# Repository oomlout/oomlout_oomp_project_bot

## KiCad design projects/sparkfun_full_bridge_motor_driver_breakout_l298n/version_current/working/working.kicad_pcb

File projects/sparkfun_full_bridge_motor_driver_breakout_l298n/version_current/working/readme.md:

# Full_Bridge_Motor_Driver_Breakout-L298N by sparkfun  
This is a harvested standardized copy of a project from github.  
The original project can be found at:  
https://github.com/sparkfun/Full_Bridge_Motor_Driver_Breakout-L298N  
Please consult that link for additional, details, files, and license information.  
Note: It was auto harvested and if the original repo had more than one board file or anything out of the ordinary the files here are likely not representative.

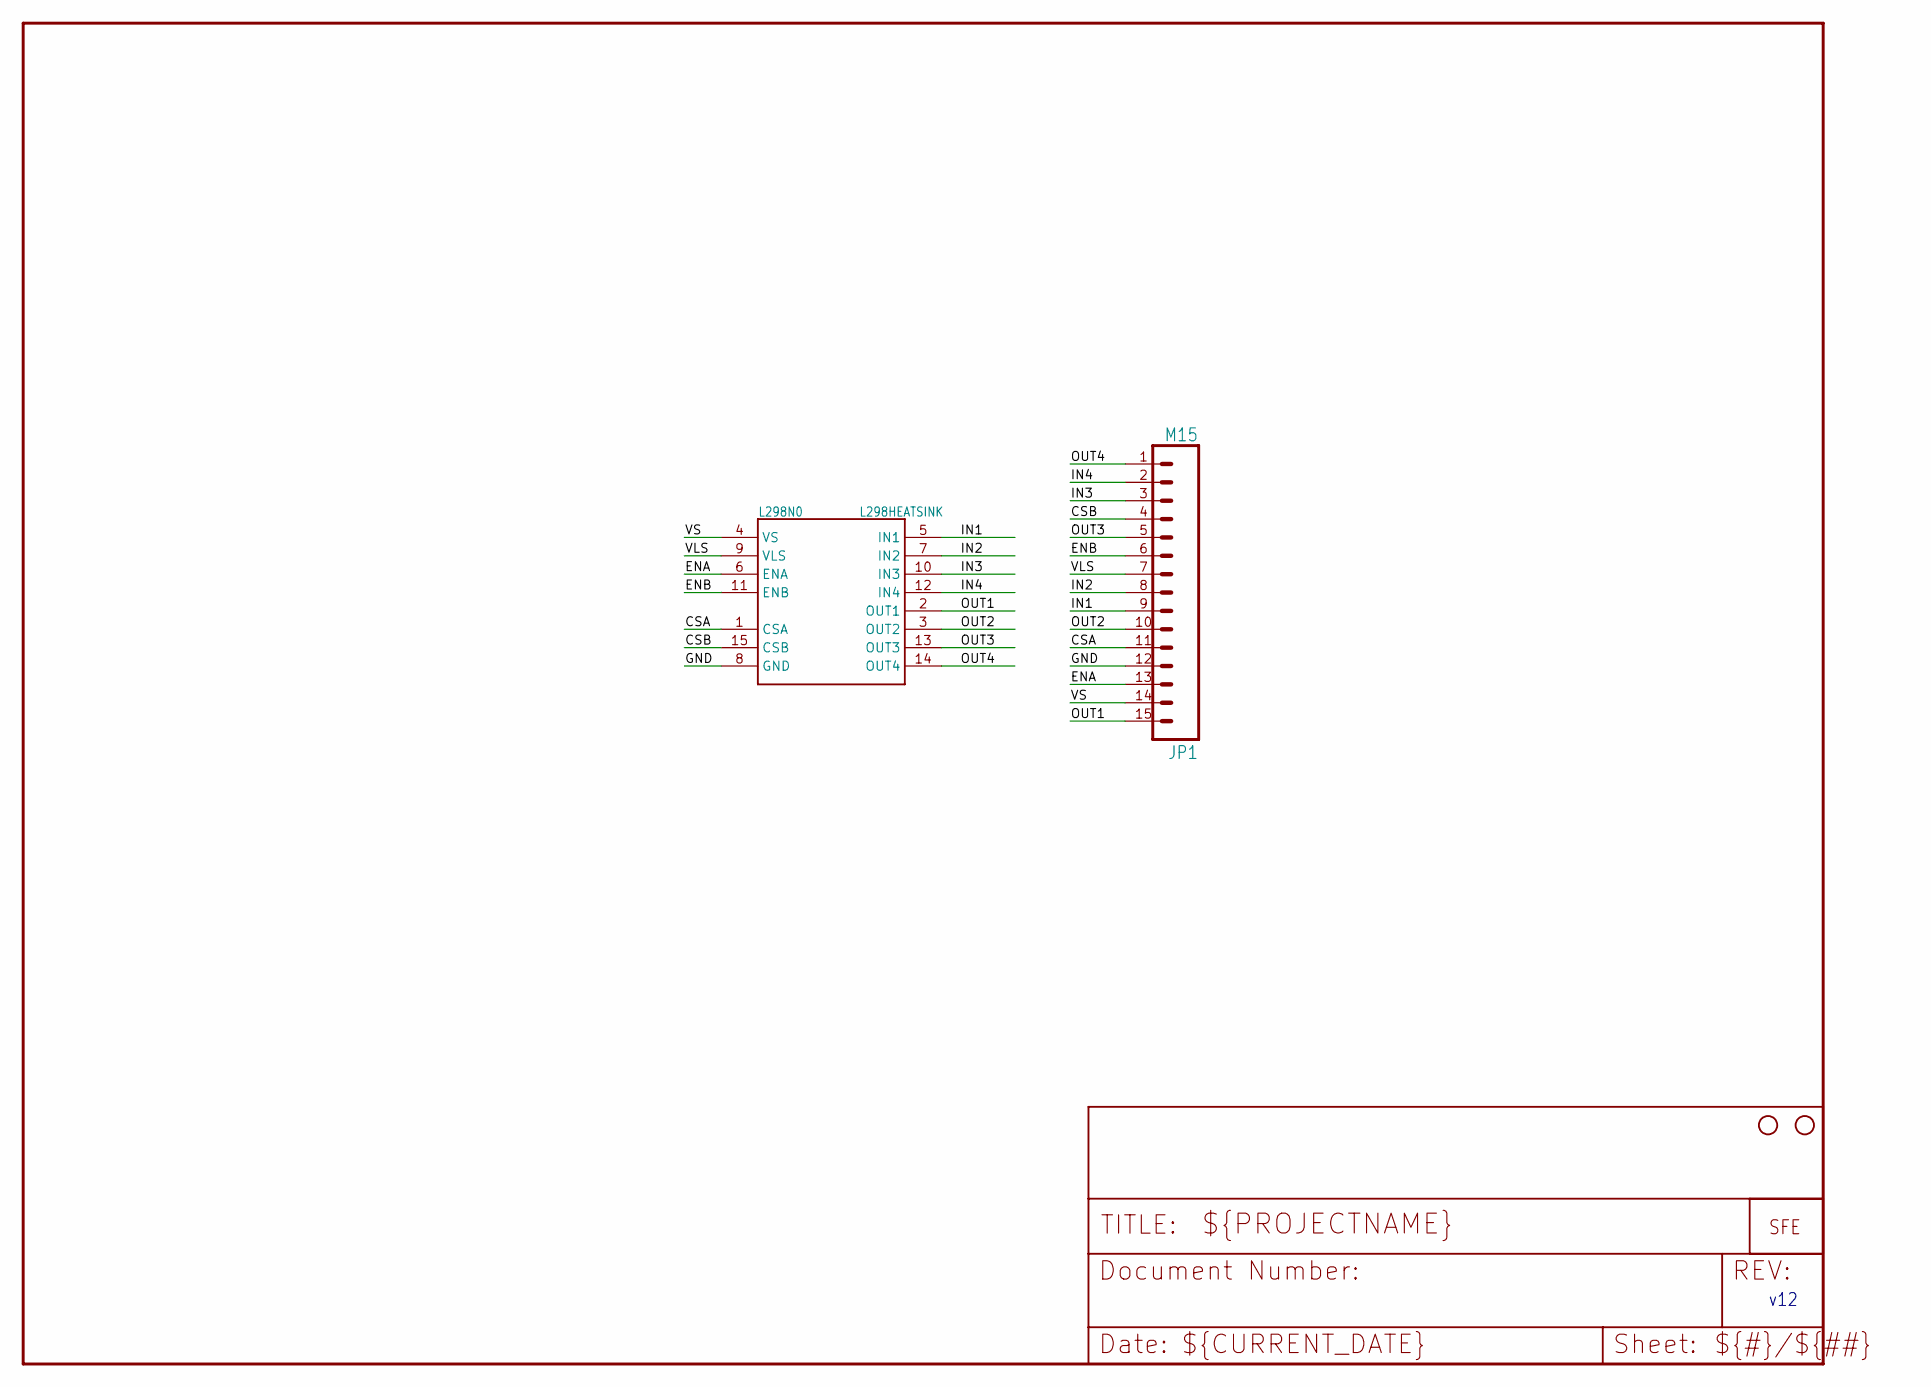
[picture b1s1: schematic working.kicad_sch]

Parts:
JP1: M15; 1X15
JP2, JP3: STAND-OFF
JP4: LOGO-SFENEW; SFE-NEW-WEBLOGO
L298N0: L298HEATSINK; MULTIWATT15_6400BGHEATSINK

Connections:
CSA: JP1.11, L298N0.1 (CSA)
CSB: JP1.4, L298N0.15 (CSB)
ENA: JP1.13, L298N0.6 (ENA)
ENB: JP1.6, L298N0.11 (ENB)
GND: JP1.12, L298N0.8 (GND)
IN1: JP1.9, L298N0.5 (IN1)
IN2: JP1.8, L298N0.7 (IN2)
IN3: JP1.3, L298N0.10 (IN3)
IN4: JP1.2, L298N0.12 (IN4)
OUT1: JP1.15, L298N0.2 (OUT1)
OUT2: JP1.10, L298N0.3 (OUT2)
OUT3: JP1.5, L298N0.13 (OUT3)
OUT4: JP1.1, L298N0.14 (OUT4)
VLS: JP1.7, L298N0.9 (VLS)
VS: JP1.14, L298N0.4 (VS)

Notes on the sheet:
v12

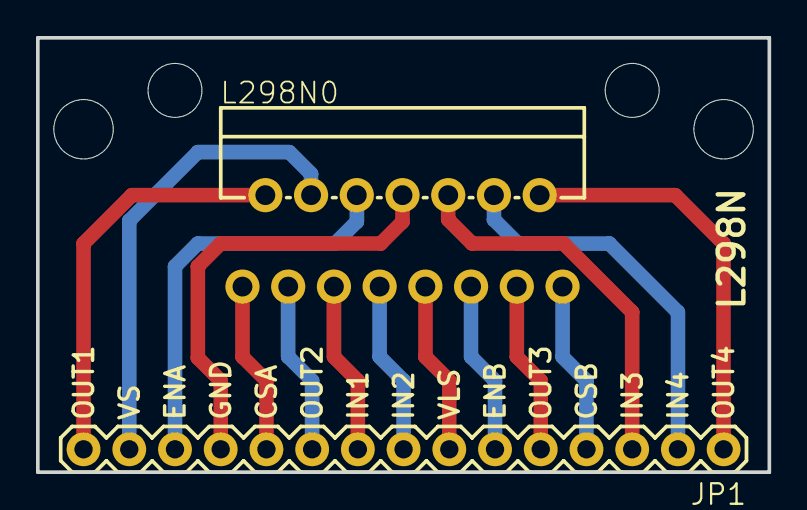
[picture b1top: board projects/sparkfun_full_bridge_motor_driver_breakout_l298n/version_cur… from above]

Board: 2 copper layers, 40.6 x 24.1 mm, 5 parts (1 on the bottom side), 15 nets.

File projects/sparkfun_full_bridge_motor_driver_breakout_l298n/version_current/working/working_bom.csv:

Row,Description,Part,References,Value,Footprint,Quantity Per PCB,Status,Datasheet
1,,LOGO-SFENEW,JP4,LOGO-SFENEW,SFE-NEW-WEBLOGO,1, ,
2,,M15,JP1,M15,1X15,1, ,
3,,STAND-OFF,JP2 JP3,STAND-OFF,STAND-OFF,2, ,
4,,L298HEATSINK,L298N0,L298HEATSINK,MULTIWATT15_6400BGHEATSINK,1, ,





Project info:
Schematic:,working
Variant:,default
Revision:,
Date:,2023-08-06_12-56-02
KiCad Version:,7.0.6-7.0.6~ubuntu22.04.1
Statistics:
Component Groups:,4
Component Count:,5 (0 SMD/ 0 THT)
Fitted Components:,5 (0 SMD/ 0 THT)
Number of PCBs:,1
Total Components:,5

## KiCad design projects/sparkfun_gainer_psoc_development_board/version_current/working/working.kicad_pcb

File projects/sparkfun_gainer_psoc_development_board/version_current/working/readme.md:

# OOMP Project  
## Gainer_PSoC_Development_Board  by sparkfun  
  
oomp key: oomp_projects_flat_sparkfun_gainer_psoc_development_board  
(snippet of original readme)  
  
SparkFun Gainer PSoC Development Board  
========================================  

[*SparkFun Gainer PSoC Development Board (DEV-08480)*](https://www.sparkfun.com/products/8480)  
  
This board utilizes the Cypress PSoC CY8C29466 IC making it a great board for digital and analog projects where AtoD and DtoA is required.  
 Simple USB interface for reprogramming - no external programmer needed.  
  
Repository Contents  
-------------------  
* **/Hardware** - All Eagle design files (.brd, .sch)  

License Information  
-------------------  
The hardware is released under [Creative Commons ShareAlike 4.0 International](https://creativecommons.org/licenses/by-sa/4.0/).  
  
Gainer is a simple board developed by Shigeru Kobayashi and the team at Gainer.cc.   
  
Distributed as-is; no warranty is given.  
  
  full source readme at [readme_src.md](readme_src.md)  
  
source repo at: [https://github.com/sparkfun/Gainer_PSoC_Development_Board](https://github.com/sparkfun/Gainer_PSoC_Development_Board)  
## Board  

## Schematic  

[schematic pdf](working_schematic.pdf)  
## Images

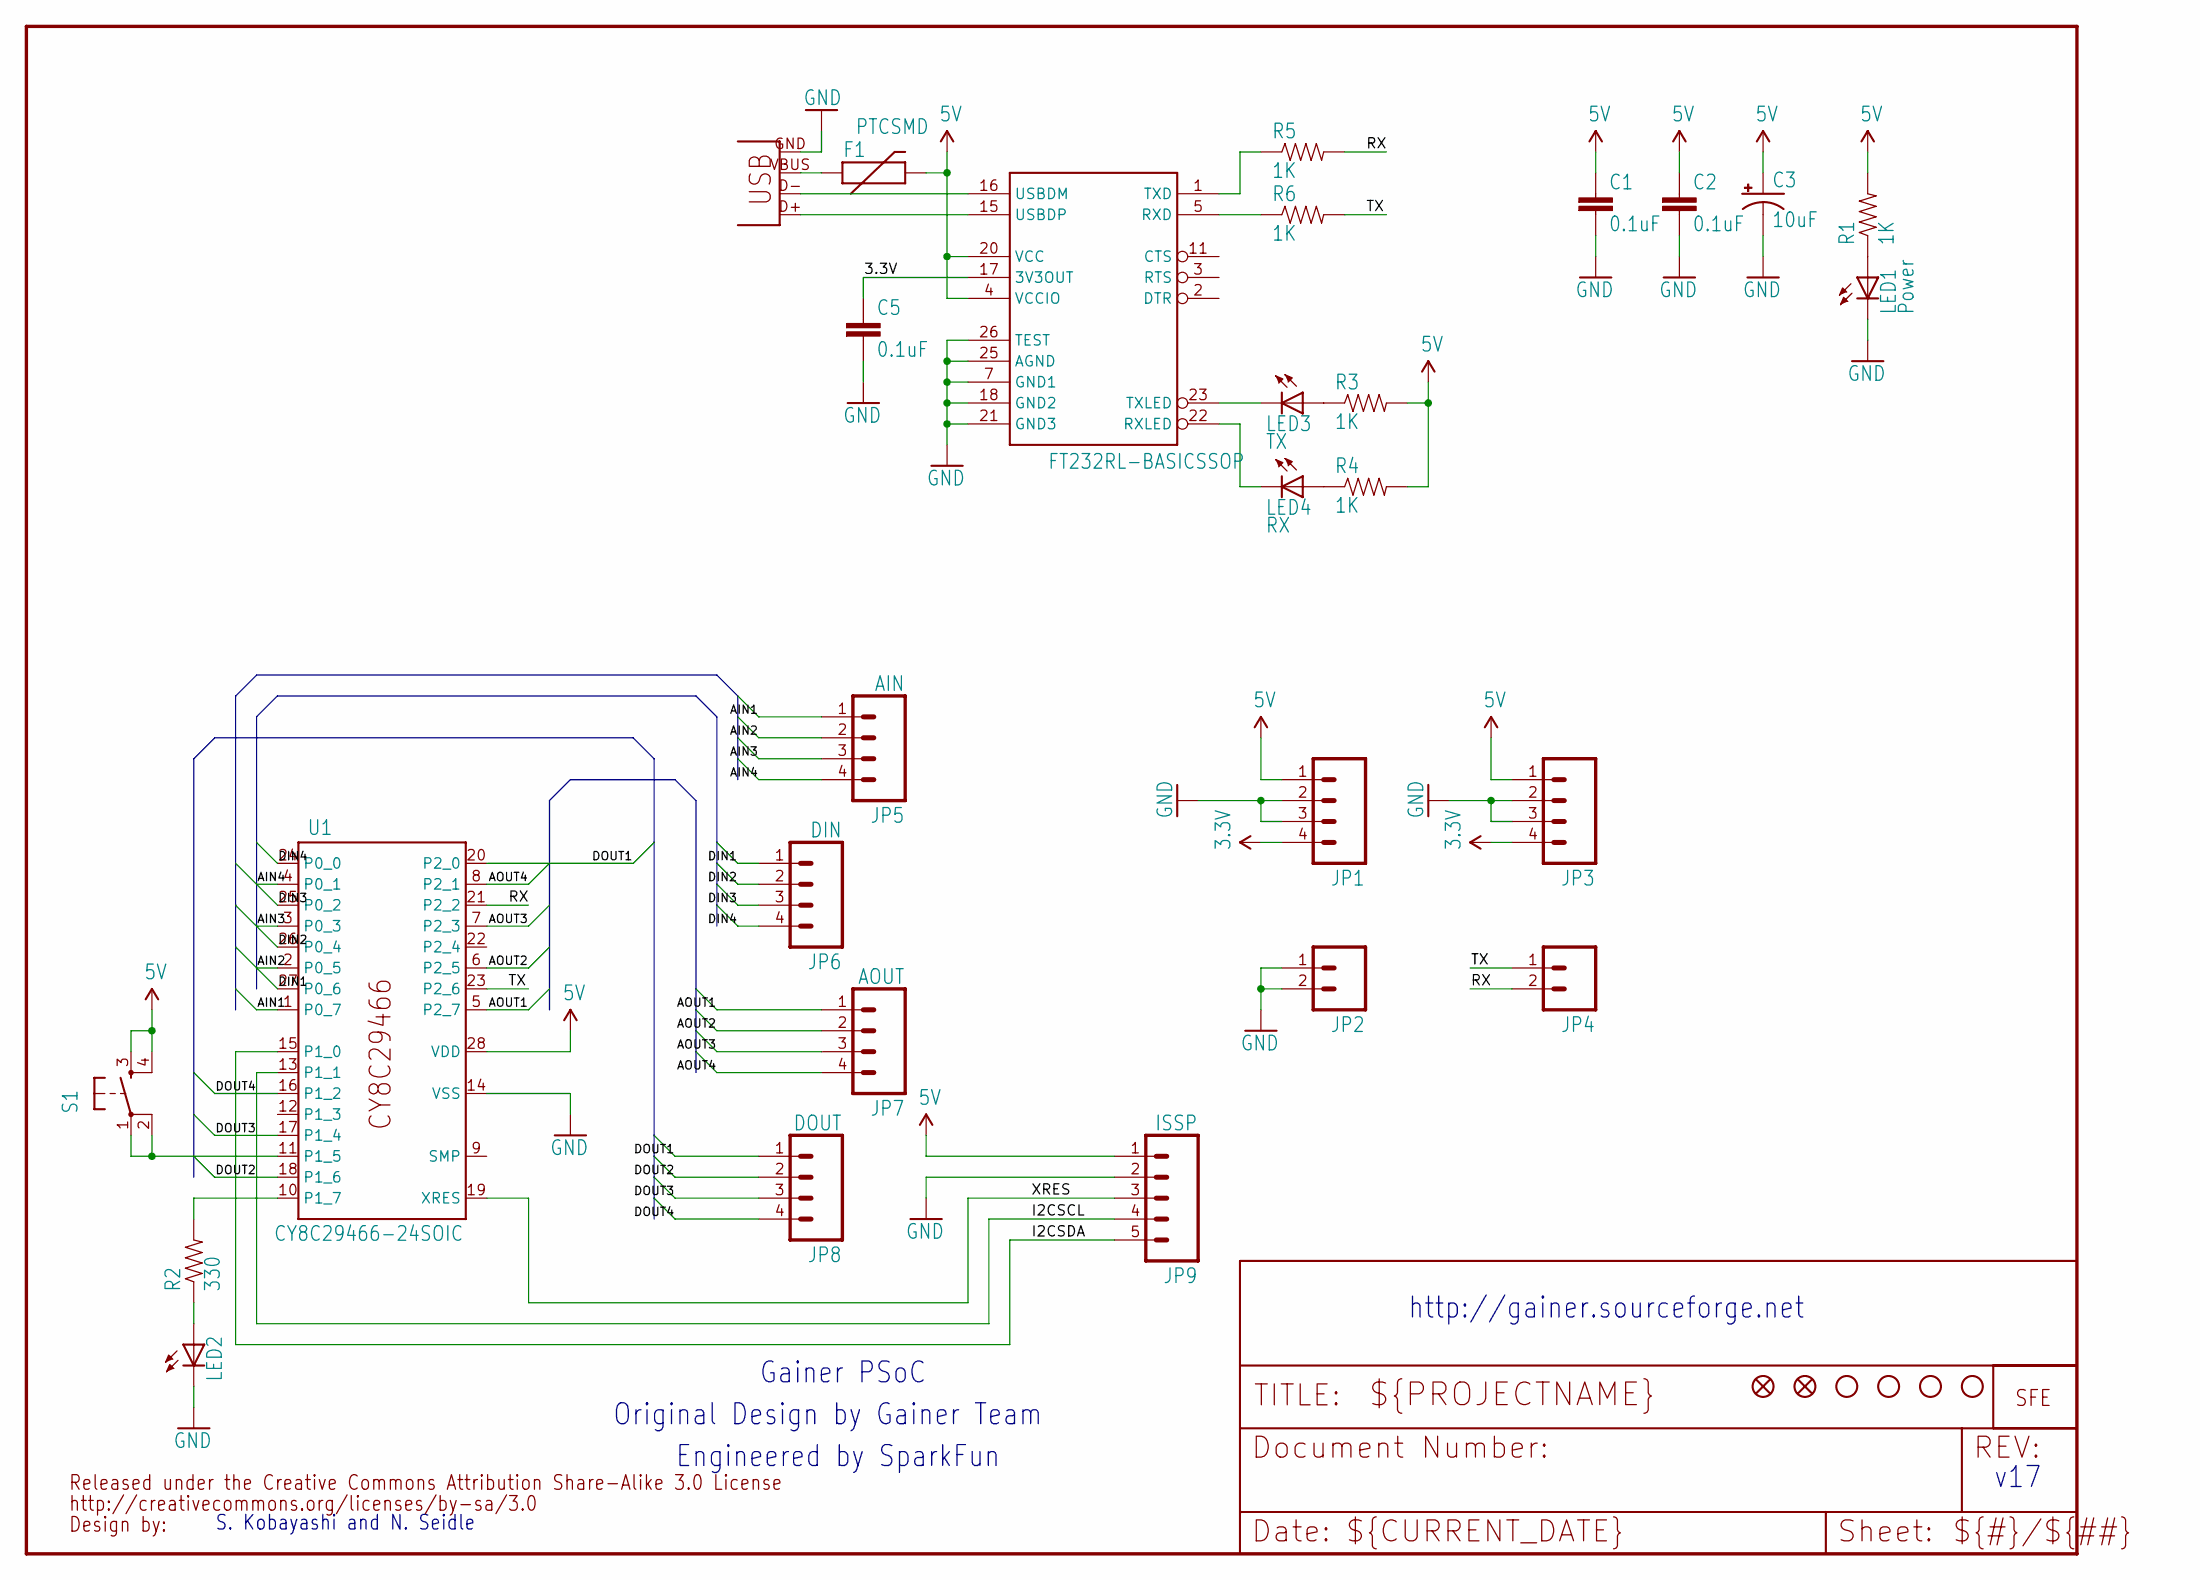
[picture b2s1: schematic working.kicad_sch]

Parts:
C1, C2, C5: 0.1uF; C0402
C3: 10uF; EIA3216
F1: PTCSMD; PTC-1206
JP1, JP3: M04PTH; 1X04
JP2, JP4: M02PTH; 1X02
JP5: AIN; 1X04
JP6: DIN; 1X04
JP7: AOUT; 1X04
JP8: DOUT; 1X04
JP9: ISSP; 1X05
LED1: Power; LED-1206
LED2: LED1206; LED-1206
LED3: TX; LED-0603
LED4: RX; LED-0603
R1, R3, R4, R5, R6: 1K; C0402
R2: 330; C0402
S1: TAC_SWITCHSMD; TACTILE_SWITCH_SMD
U1: CY8C29466-24SOIC; SOIC28
U2: FT232RL-BASICSSOP; SSOP28DB
U$1: LOGO-SFENEW; SFE-NEW-WEBLOGO
U$10, U$17: FIDUCIAL1X2; FIDUCIAL-1X2
U$12, U$13, U$14, U$15: STAND-OFF
U$18: CREATIVE_COMMONS
X2: USBSMD; USB-MINIB

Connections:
3.3V: C5.1, JP1.4, JP3.4, U2.17 (3V3OUT)
5V: C1.1, C2.1, C3.A (+), F1.2, JP1.1, JP3.1, JP9.1, R1.2, R3.2, R4.2, S1.3, S1.4, U1.28 (VDD), U2.4 (VCCIO), U2.20 (VCC)
AIN1: JP5.1, U1.1 (P0_7)
AIN2: JP5.2, U1.2 (P0_5)
AIN3: JP5.3, U1.3 (P0_3)
AIN4: JP5.4, U1.4 (P0_1)
AOUT1: JP7.1, U1.5 (P2_7)
AOUT2: JP7.2, U1.6 (P2_5)
AOUT3: JP7.3, U1.7 (P2_3)
AOUT4: JP7.4, U1.8 (P2_1)
DIN1: JP6.1, U1.27 (P0_6)
DIN2: JP6.2, U1.26 (P0_4)
DIN3: JP6.3, U1.25 (P0_2)
DIN4: JP6.4, U1.24 (P0_0)
DOUT1: JP8.1, U1.20 (P2_0)
DOUT2: JP8.2, U1.18 (P1_6)
DOUT3: JP8.3, U1.17 (P1_4)
DOUT4: JP8.4, U1.16 (P1_2)
GND: C1.2, C2.2, C3.C (-), C5.2, JP1.2, JP1.3, JP2.1, JP2.2, JP3.2, JP3.3, JP9.2, LED1.C, LED2.C, U1.14 (VSS), U2.7 (GND1), U2.18 (GND2), U2.21 (GND3), U2.25 (AGND), U2.26 (TEST), X2.GND
I2CSCL: JP9.4, U1.13 (P1_1)
I2CSDA: JP9.5, U1.15 (P1_0)
unnamed: LED3.A, R3.1
unnamed: F1.1, X2.VBUS
unnamed: LED1.A, R1.1
unnamed: LED4.A, R4.1
unnamed: R6.1, U2.5 (RXD)
unnamed: LED4.C, U2.22 (RXLED)
unnamed: S1.1, S1.2, U1.11 (P1_5)
unnamed: R2.2, U1.10 (P1_7)
unnamed: LED2.A, R2.1
unnamed: U2.16 (USBDM), X2.D-
unnamed: U2.15 (USBDP), X2.D+
unnamed: R5.1, U2.1 (TXD)
unnamed: LED3.C, U2.23 (TXLED)
RX: JP4.2, R5.2, U1.21 (P2_2)
TX: JP4.1, R6.2, U1.23 (P2_6)
XRES: JP9.3, U1.19 (XRES)

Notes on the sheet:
Engineered by SparkFun
http://gainer.sourceforge.net
Gainer PSoC
Original Design by Gainer Team
v17
S. Kobayashi and N. Seidle

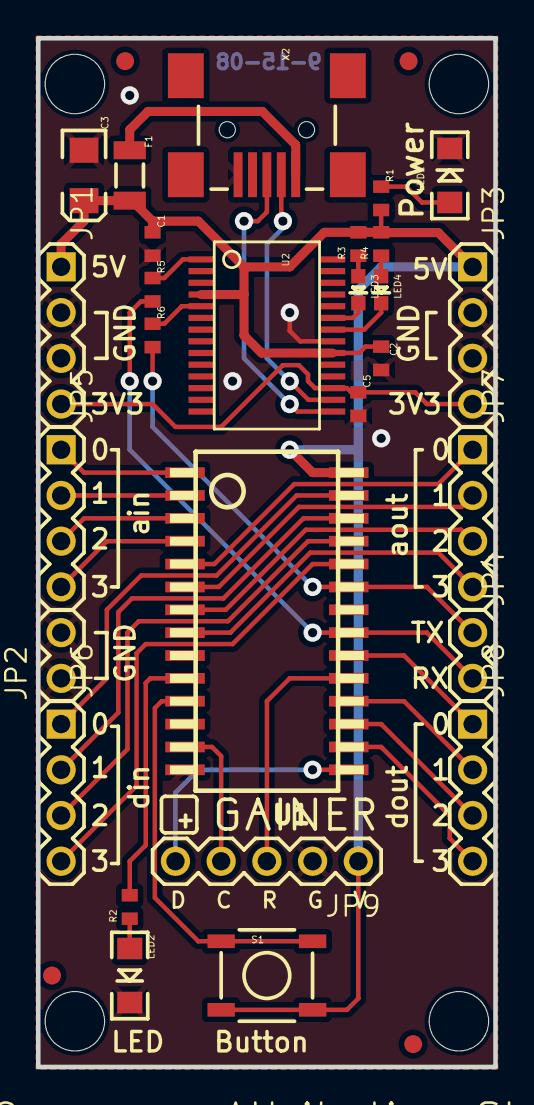
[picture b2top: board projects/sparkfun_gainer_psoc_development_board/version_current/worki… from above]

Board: 2 copper layers, 25.4 x 57.1 mm, 39 parts (1 on the bottom side), 37 nets.

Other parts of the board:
E$1, E$2: FIDUCIAL-1X2
U$19: GAINER_LOGO

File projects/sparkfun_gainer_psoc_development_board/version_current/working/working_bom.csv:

Row,Description,Part,References,Value,Footprint,Quantity Per PCB,Status,Datasheet
1,,CAP0402,C1 C2 C5,0.1uF,C0402,3, ,
2,,CAP_POL1206,C3,10uF,EIA3216,1, ,
3,,PTCSMD,F1,PTCSMD,PTC-1206,1, ,
4,,M04PTH,JP5,AIN,1X04,1, ,
5,,M04PTH,JP7,AOUT,1X04,1, ,
6,,M04PTH,JP6,DIN,1X04,1, ,
7,,M04PTH,JP8,DOUT,1X04,1, ,
8,,M05,JP9,ISSP,1X05,1, ,
9,,M02PTH,JP2 JP4,M02PTH,1X02,2, ,
10,,M04PTH,JP1 JP3,M04PTH,1X04,2, ,
11,,LED1206,LED2,LED1206,LED-1206,1, ,
12,,LED1206,LED1,Power,LED-1206,1, ,
13,,LED0603,LED4,RX,LED-0603,1, ,
14,,LED0603,LED3,TX,LED-0603,1, ,
15,,RESISTOR0402,R2,330,C0402,1, ,
16,,RESISTOR0402,R1 R3 R4 R5 R6,1K,C0402,5, ,
17,,TAC_SWITCHSMD,S1,TAC_SWITCHSMD,TACTILE_SWITCH_SMD,1, ,
18,,CY8C29466-24SOIC,U1,CY8C29466-24SOIC,SOIC28,1, ,
19,,FT232RL-BASICSSOP,U2,FT232RL-BASICSSOP,SSOP28DB,1, ,
20,,CREATIVE_COMMONS,U$18,CREATIVE_COMMONS,CREATIVE_COMMONS,1, ,
21,,LOGO-SFENEW,U$1,LOGO-SFENEW,SFE-NEW-WEBLOGO,1, ,
22,,STAND-OFF,U$12 U$13 U$14 U$15,STAND-OFF,STAND-OFF,4, ,
23,,USBSMD,X2,USBSMD,USB-MINIB,1, ,





Project info:
Schematic:,working
Variant:,default
Revision:,
Date:,2023-08-06_12-56-02
KiCad Version:,7.0.6-7.0.6~ubuntu22.04.1
Statistics:
Component Groups:,23
Component Count:,34 (0 SMD/ 0 THT)
Fitted Components:,34 (0 SMD/ 0 THT)
Number of PCBs:,1
Total Components:,34

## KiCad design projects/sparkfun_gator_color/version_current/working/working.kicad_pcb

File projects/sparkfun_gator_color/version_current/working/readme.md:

# OOMP Project  
## gator_color  by sparkfun  
  
oomp key: oomp_projects_flat_sparkfun_gator_color  
(snippet of original readme)  
  
SparkFun gator:color  
========================================  

[*SparkFun gator:color - COM-14890*](https://www.sparkfun.com/products/14890)  
  
The gator:color a smattering of LEDs into an alligator clippable format for use with micro:bit as well as the gator:bit expansion for micro:bit.  
  
Repository Contents  
-------------------  
* **/Firmware** - Example code used with the gator:color. While they are compiled HEX codes, you can modify the example code once they are imported into MakeCode editor.  
* **/Hardware** - Eagle design files (.brd, .sch)  
* **/Production** - Production panel files (.brd)  
  
Documentation  
--------------  
* **[Hookup Guide](https://learn.sparkfun.com/tutorials/gatorcolor-protosnap-hookup-guide)** - Basic hookup guide for the gator:color.  
  
Product Versions  
----------------  
* [COM-14890](https://www.sparkfun.com/products/14890)- The gator:color allows you to gator-clip to LED's.  
  
License Information  
-------------------  
  
This product is _**open source**_!   
  
Please review the LICENSE.md file for license information.   
  
If you have any questions or concerns on licensing, please contact techsupport@sparkfun.com.  
  
Distributed as-is; no warranty is given.  
  
- Your friends at SparkFun.  
  
_<COLLABORATION CREDIT>_  
  
  full source readme at [readme_src.md](readme_src.md)  
  
source repo at: [https://github.com/sparkfun/gator_color](https://github.com/sparkfun/gator_color)  
## Board  

## Schematic  

[schematic pdf](working_schematic.pdf)  
## Images

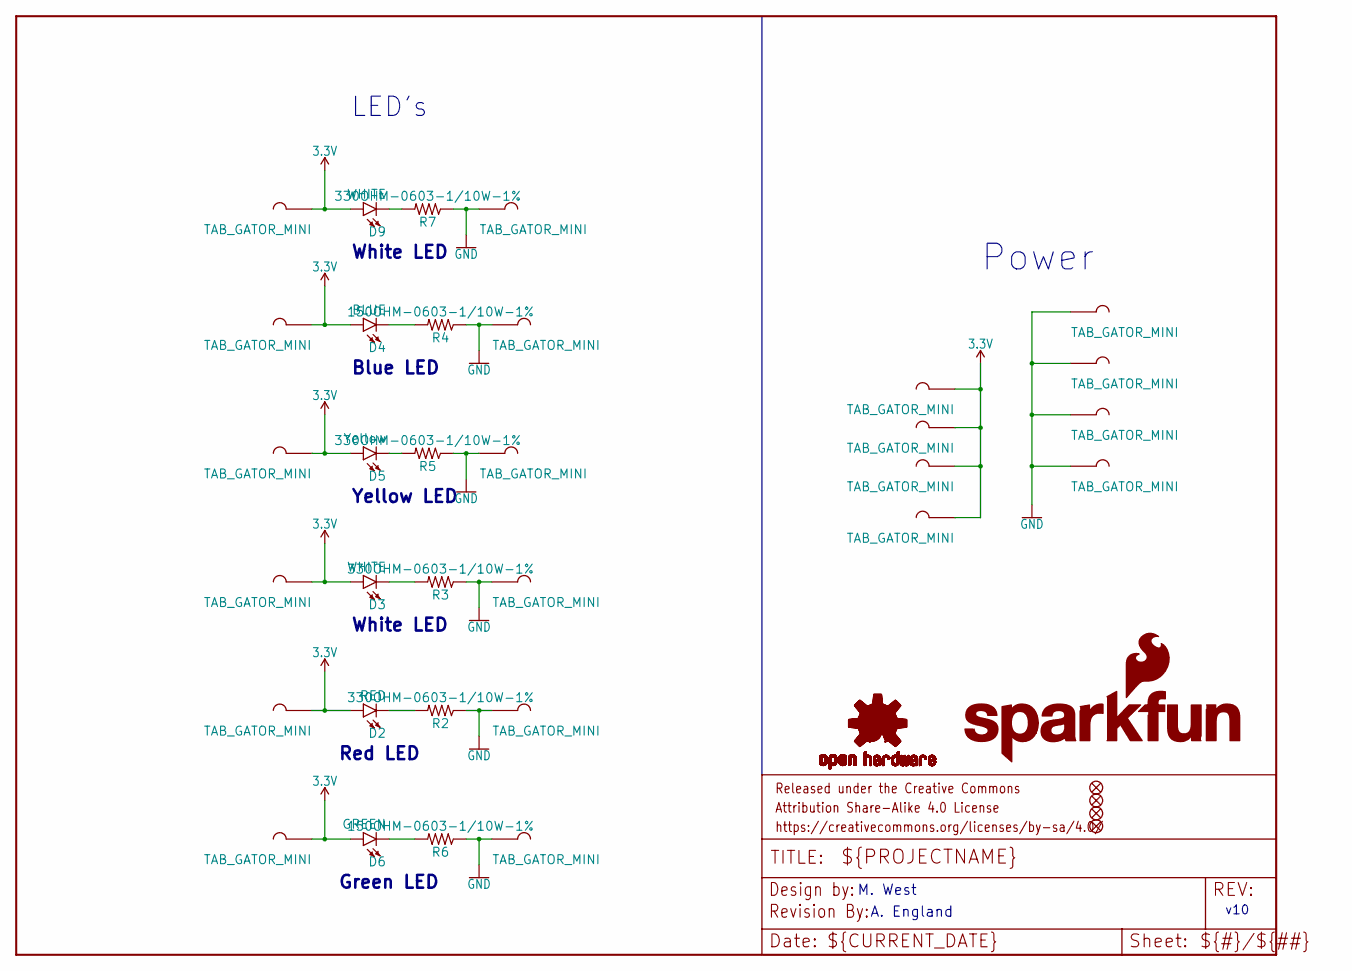
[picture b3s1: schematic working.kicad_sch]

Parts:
D2: RED; LED-1206
D3, D9: WHITE; LED-1206
D4: BLUE; LED-1206
D5: Yellow; LED-1206
D6: GREEN; LED-1206
FD1, FD2, FD3, FD4: FIDUCIALUFIDUCIAL; FIDUCIAL-MICRO
FRAME1: FRAME-LETTER; CREATIVE_COMMONS
LOGO1: SFE_LOGO_FLAME.1_INCH; SFE_LOGO_FLAME_.1
LOGO2, LOGO15: OSHW-LOGOMINI; OSHW-LOGO-MINI
LOGO8: REVISION
LOGO16: SFE_LOGO_NAME.1_INCH; SFE_LOGO_NAME_.1
R2, R3, R5, R7: 330OHM-0603-1/10W-1%; 0603
R4, R6: 150OHM-0603-1/10W-1%; 0603
U$1, U$2, U$3, U$6, U$7, U$8, U$10, U$11, U$13, U$16, U$18, U$19, U$20, U$21, U$28, U$30, U$32, U$33, U$34, U$38: TAB_GATOR_MINI

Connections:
3.3V: D2.A, D3.A, D4.A, D5.A, D6.A, D9.A, U$10.P1, U$13.P1, U$16.P1, U$18.P1, U$19.P1, U$20.P1, U$21.P1, U$32.P1, U$33.P1, U$34.P1
GND: R2.1, R3.1, R4.1, R5.1, R6.1, R7.1, U$1.P1, U$2.P1, U$3.P1, U$6.P1, U$7.P1, U$8.P1, U$11.P1, U$28.P1, U$30.P1, U$38.P1
unnamed: D2.C, R2.2
unnamed: D3.C, R3.2
unnamed: D4.C, R4.2
unnamed: D5.C, R5.2
unnamed: D6.C, R6.2
unnamed: D9.C, R7.2

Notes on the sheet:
Power
White LED
Red LED
Green LED
Blue LED
Yellow LED
LED's
v10
M. West
A. England

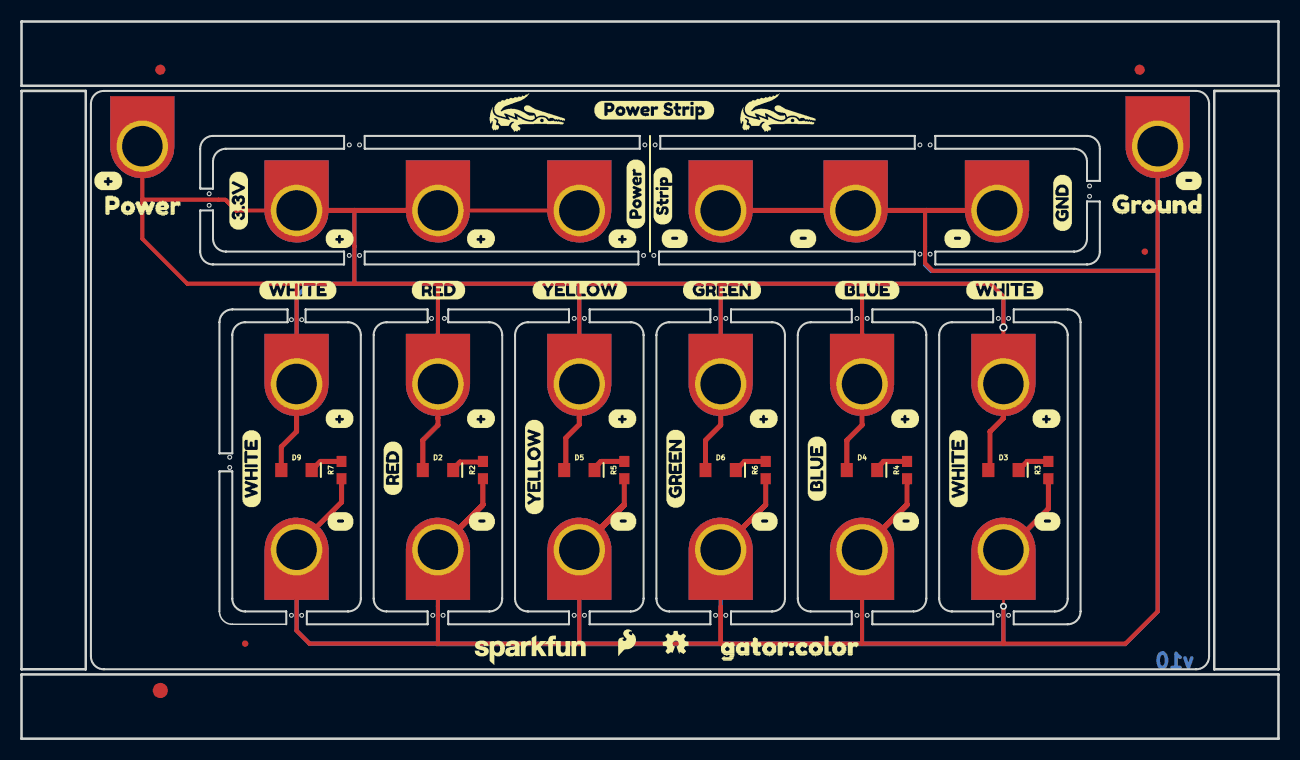
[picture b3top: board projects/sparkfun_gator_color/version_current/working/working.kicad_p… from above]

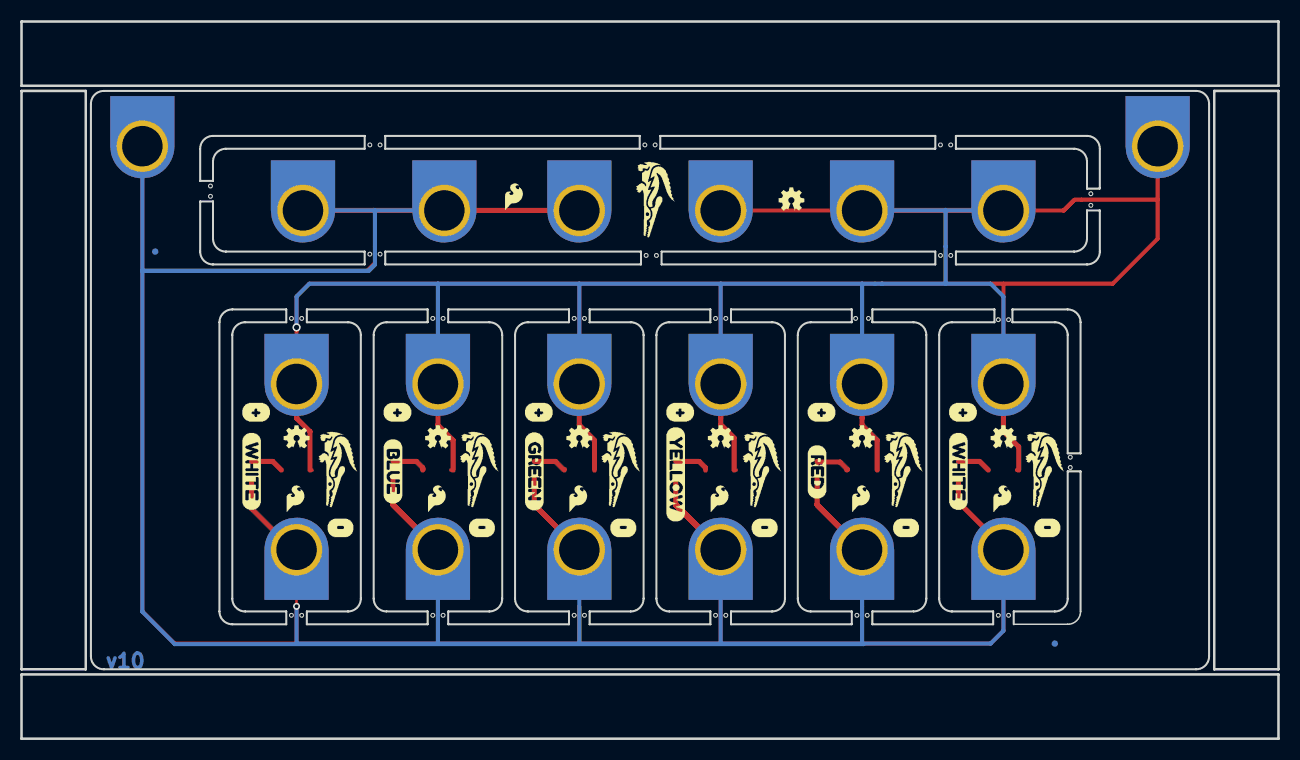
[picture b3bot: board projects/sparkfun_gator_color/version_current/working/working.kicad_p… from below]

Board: 2 copper layers, 124.2 x 70.9 mm, 165 parts (41 on the bottom side), 8 nets.

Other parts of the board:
@HOLE0, @HOLE1, @HOLE2, @HOLE3, @HOLE4, @HOLE5, @HOLE6, @HOLE7, @HOLE8, @HOLE9, @HOLE10, @HOLE11, @HOLE12, @HOLE13, @HOLE14, @HOLE15, @HOLE16, @HOLE17, @HOLE18, @HOLE19, @HOLE20, @HOLE21, @HOLE22, @HOLE23, @HOLE24, @HOLE25, @HOLE26, @HOLE27, @HOLE28, @HOLE29, @HOLE30, @HOLE31, @HOLE32, @HOLE33, @HOLE34, @HOLE35, @HOLE36, @HOLE37, @HOLE38, @HOLE39, @HOLE40, @HOLE41: (no value)
E$1, E$2: FIDUCIAL-1X2
E$3: FIDUCIAL-1.5X3
LOGO3, LOGO4, LOGO5, LOGO6, LOGO7, LOGO18: OSHW-LOGOMINI; OSHW-LOGO-MINI
LOGO9, LOGO10, LOGO11, LOGO12, LOGO13, LOGO17, LOGO19: SFE_LOGO_FLAME.1_INCH; SFE_LOGO_FLAME_.1
U$5: POWER_STRIP0
U$9: GROUND3
U$12, U$14, U$15, U$53, U$55, U$57, U$60, U$62, U$64, U$77, U$81, U$83, U$84, U$85, U$86, U$87: #8
U$17, U$41, U$42: RED2
U$22, U$23, U$24, U$54, U$56, U$58, U$61, U$63, U$65, U$82, U$89, U$90, U$91, U$92, U$93, U$95: #9
U$25: 3#3V1
U$26: GND0
U$27: POWER1
U$29, U$31, U$50, U$68, U$69, U$70, U$71, U$72, U$73: GATOR#PNG
U$35: STRIP2
U$36, U$37, U$75: BLUE4
U$39, U$40, U$67: GREEN3
U$43: POWER2
U$44, U$45, U$46, U$47, U$78, U$79: WHITE6
U$48, U$49, U$76: YELLOW5
U$51: GATOR#COLOR0

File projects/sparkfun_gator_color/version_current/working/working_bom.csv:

Row,Description,Part,References,Value,Footprint,Quantity Per PCB,Status,Datasheet
1,,LED-BLUE1206,D4,BLUE,LED-1206,1, ,
2,,LED-GREEN1206,D6,GREEN,LED-1206,1, ,
3,,LED-RED1206,D2,RED,LED-1206,1, ,
4,,LED-WHITE1206,D3 D9,WHITE,LED-1206,2, ,
5,,LED-YELLOWLILYPAD,D5,Yellow,LED-1206,1, ,
6,,FRAME-LETTER,FRAME1,FRAME-LETTER,CREATIVE_COMMONS,1, ,
7,,OSHW-LOGOMINI,LOGO2 LOGO15,OSHW-LOGOMINI,OSHW-LOGO-MINI,2, ,
8,,REVISION,LOGO8,REVISION,REVISION,1, ,
9,,SFE_LOGO_FLAME.1_INCH,LOGO1,SFE_LOGO_FLAME.1_INCH,SFE_LOGO_FLAME_.1,1, ,
10,,SFE_LOGO_NAME.1_INCH,LOGO16,SFE_LOGO_NAME.1_INCH,SFE_LOGO_NAME_.1,1, ,
11,,150OHM-0603-1/10W-1%,R4 R6,150OHM-0603-1/10W-1%,0603,2, ,
12,,330OHM-0603-1/10W-1%,R2 R3 R5 R7,330OHM-0603-1/10W-1%,0603,4, ,
13,,TAB_GATOR_MINI,U$1 U$2 U$3 U$6 U$7 U$8 U$10 U$11 U$13 U$16 U$18 U$19 U$20 U$21 U$28 U$30 U$32 U$33 U$34 U$38,TAB_GATOR_MINI,TAB_GATOR_MINI,20, ,





Project info:
Schematic:,working
Variant:,default
Revision:,
Date:,2023-08-06_12-56-02
KiCad Version:,7.0.6-7.0.6~ubuntu22.04.1
Statistics:
Component Groups:,13
Component Count:,38 (0 SMD/ 0 THT)
Fitted Components:,38 (0 SMD/ 0 THT)
Number of PCBs:,1
Total Components:,38

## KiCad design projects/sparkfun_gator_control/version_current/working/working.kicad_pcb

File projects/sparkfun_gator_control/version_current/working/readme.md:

# gator_control by sparkfun  
This is a harvested standardized copy of a project from github.  
The original project can be found at:  
https://github.com/sparkfun/gator_control  
Please consult that link for additional, details, files, and license information.  
Note: It was auto harvested and if the original repo had more than one board file or anything out of the ordinary the files here are likely not representative.

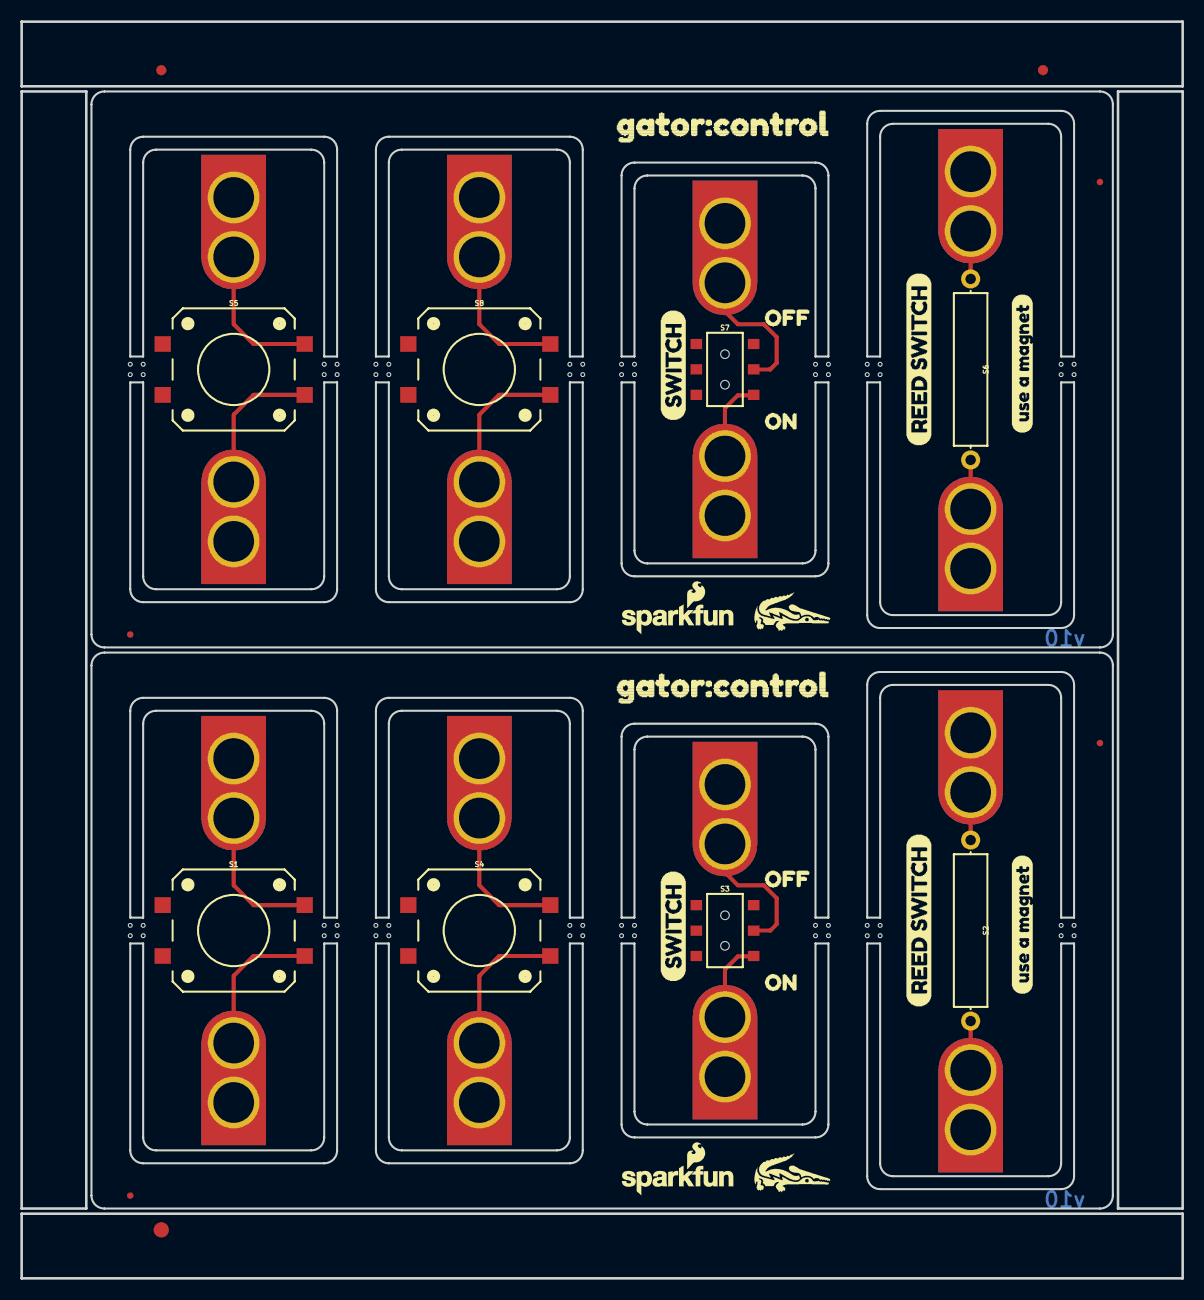
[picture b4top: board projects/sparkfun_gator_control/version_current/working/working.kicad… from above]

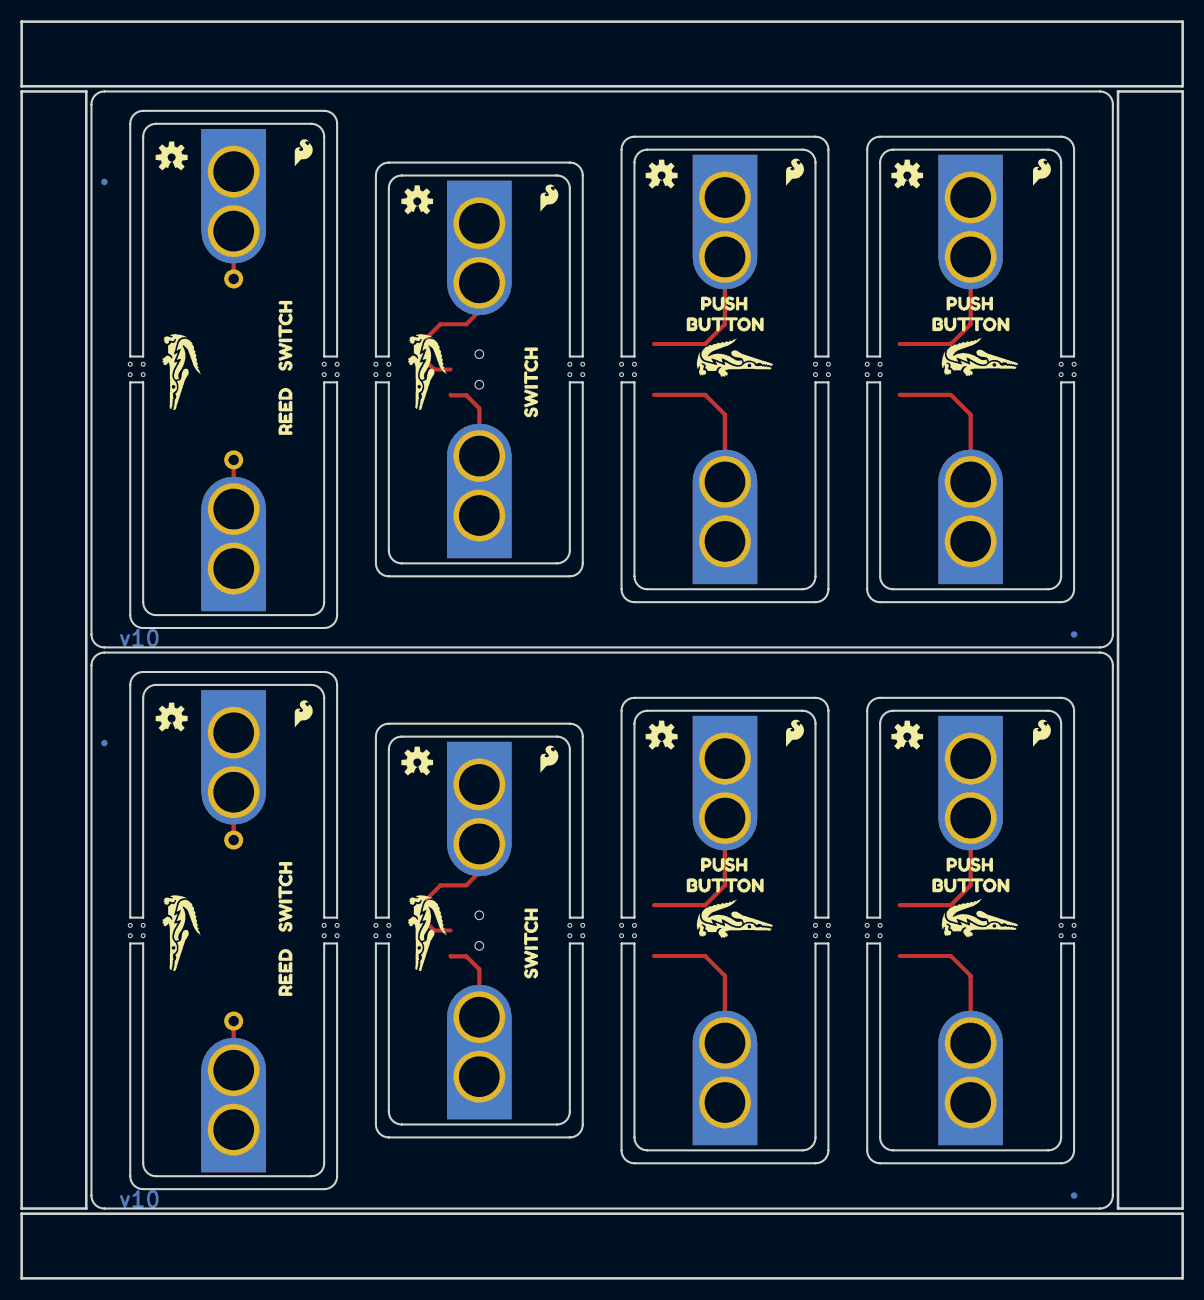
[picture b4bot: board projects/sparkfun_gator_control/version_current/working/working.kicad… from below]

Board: 2 copper layers, 114.0 x 123.4 mm, 153 parts (42 on the bottom side), 16 nets.

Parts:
@HOLE0, @HOLE1, @HOLE2, @HOLE3, @HOLE4, @HOLE5, @HOLE6, @HOLE7, @HOLE8, @HOLE9, @HOLE10, @HOLE11, @HOLE12, @HOLE13, @HOLE14, @HOLE15, @HOLE16, @HOLE17, @HOLE18, @HOLE19, @HOLE20, @HOLE21, @HOLE22, @HOLE23, @HOLE24, @HOLE25, @HOLE26, @HOLE27, @HOLE28, @HOLE29, @HOLE30, @HOLE31, @HOLE32, @HOLE33, @HOLE34, @HOLE35, @HOLE36, @HOLE37, @HOLE38, @HOLE39, @HOLE40, @HOLE41, @HOLE42, @HOLE43, @HOLE44, @HOLE45, @HOLE46, @HOLE47, @HOLE48, @HOLE49, @HOLE50, @HOLE51, @HOLE52, @HOLE53, @HOLE54, @HOLE55, @HOLE56, @HOLE57, @HOLE58, @HOLE59, @HOLE60, @HOLE61, @HOLE62, @HOLE63: (no value)
E$1, E$2: FIDUCIAL-1X2
E$3: FIDUCIAL-1.5X3
FD1, FD2, FD3, FD4, FD5, FD6, FD7, FD8: FIDUCIALUFIDUCIAL; FIDUCIAL-MICRO
LOGO1, LOGO4, LOGO6, LOGO7, LOGO9, LOGO12, LOGO14, LOGO15: SFE_LOGO_FLAME.1_INCH; SFE_LOGO_FLAME_.1
LOGO2, LOGO3, LOGO5, LOGO8, LOGO10, LOGO11, LOGO13, LOGO16: OSHW-LOGOS; OSHW-LOGO-S
S1, S4, S5, S8: MOMENTARY-SWITCH-SPST-SMD-12MM; TACTILE_SWITCH_SMD_12MM
S2, S6: REED_SWITCH-PTH-INSULATED; REED_SWITCH_PLASTIC
S3, S7: SWITCH_DPDT_SMD_AYZ0202
U$1, U$22, U$25, U$26, U$27, U$28, U$29, U$38, U$51, U$70: GATOR#PNG
U$2, U$5, U$39, U$42: BUTTON3
U$3, U$4, U$40, U$41: PUSH4
U$6, U$46: OFF9
U$7, U$43: REED_SWITCH0
U$8, U$44: SWITCH2
U$9, U$45: USE_A_MAGNET10
U$10, U$11, U$12, U$14, U$15, U$16, U$17, U$19, U$30, U$31, U$32, U$33, U$34, U$35, U$36, U$37: GATOR
U$13, U$47: ON8
U$18, U$21, U$48, U$50: SWITCH5
U$20, U$49: REED6
U$23, U$52: GATOR#CONTROL0
U$24, U$53: SFE_LOGO_NAME_FLAME_.1

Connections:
unnamed: S4.1, U$19.P$1, U$19.P$2
unnamed: S4.3, U$10.P$1, U$10.P$2
unnamed: S1.1, U$17.P$1, U$17.P$2
unnamed: S1.3, U$11.P$1, U$11.P$2
unnamed: S2.P$1, U$16.P$1, U$16.P$2
unnamed: S2.P$2, U$12.P$1, U$12.P$2
unnamed: S3.2, U$15.P$1, U$15.P$2
unnamed: S3.3, U$14.P$1, U$14.P$2
unnamed: S8.1, U$37.P$1, U$37.P$2
unnamed: S8.3, U$30.P$1, U$30.P$2
unnamed: S5.1, U$36.P$1, U$36.P$2
unnamed: S5.3, U$31.P$1, U$31.P$2
unnamed: S6.P$1, U$35.P$1, U$35.P$2
unnamed: S6.P$2, U$32.P$1, U$32.P$2
unnamed: S7.2, U$34.P$1, U$34.P$2
unnamed: S7.3, U$33.P$1, U$33.P$2

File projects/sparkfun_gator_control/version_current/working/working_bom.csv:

Row,Description,Part,References,Value,Footprint,Quantity Per PCB,Status,Datasheet
1,,FRAME-LETTER,FRAME1,FRAME-LETTER,CREATIVE_COMMONS,1, ,
2,,OSHW-LOGOS,LOGO2,OSHW-LOGOS,OSHW-LOGO-S,1, ,
3,,REVISION,LOGO9,REVISION,REVISION,1, ,
4,,SFE_LOGO_FLAME.1_INCH,LOGO1,SFE_LOGO_FLAME.1_INCH,SFE_LOGO_FLAME_.1,1, ,
5,,MOMENTARY-SWITCH-SPST-SMD-12MM,S1 S4,MOMENTARY-SWITCH-SPST-SMD-12MM,TACTILE_SWITCH_SMD_12MM,2, ,
6,,REED_SWITCH-PTH-INSULATED,S2,REED_SWITCH-PTH-INSULATED,REED_SWITCH_PLASTIC,1, ,
7,,SWITCH-SPDT-SMD-AYZ0202,S3,SWITCH-SPDT-SMD-AYZ0202,SWITCH_DPDT_SMD_AYZ0202,1, ,
8,,GATOR,U$10 U$11 U$12 U$14 U$15 U$16 U$17 U$19,GATOR,GATOR,8, ,





Project info:
Schematic:,working
Variant:,default
Revision:,
Date:,2023-08-06_12-56-02
KiCad Version:,7.0.6-7.0.6~ubuntu22.04.1
Statistics:
Component Groups:,8
Component Count:,16 (0 SMD/ 0 THT)
Fitted Components:,16 (0 SMD/ 0 THT)
Number of PCBs:,1
Total Components:,16

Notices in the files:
projects/sparkfun_gainer_psoc_development_board/version_current/working/working.kicad_sch:
http://creativecommons.org/licenses/by-sa/3.0
Released under the Creative Commons Attribution Share-Alike 3.0 License
parts and their libraries:
Released under the Creative Commons Attribution Share-Alike 4.0 License
